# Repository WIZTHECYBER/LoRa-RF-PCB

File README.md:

# LoRa-RF-PCB

A custom PCB for long range radio frequency (LoRa) communication, built around an RP2040 and a Semtech SX1262 radio.

## Overview

I saw a guideline for a LoRa RF devboard in Forge Blueprint and decided to make my own. I did made schematics with help of AI and then designed and routed the PCB myself!!

###This PCB contains following components###
|MCU, radio, and flash all on one PCB, powered and programmed over USB-C.|

## Schematics Components 

| Part | Role |
|---|---|
| RP2040 | Microcontroller — runs everything |
| SX1262 | LoRa radio chip — handles the actual RF signal |
| 16MB flash | Stores the firmware |
| USB-C | Power and programming |
| RF switch + filter + antenna | Gets the signal in and out cleanly |
| Crystal oscillators | Reference clocks for the MCU and radio |
| LDO regulator | Power supply |
| Boot / Reset buttons | Standard flashing controls |

## Build Journey

This was my first time working with a 4-layer PCB, and it showed me why layer count matters — figuring it out took a while, but I learned a lot along the way. I used **Gemini** for help with the schematics.

From there, I moved on to placing components and routing the PCB myself. 

RF signal paths need to be straight and length-matched, which made that part of the routing genuinely tricky — it took about 2 days to fully route the board. Once the hardware was done, I wrote the firmware to bring it to life.

## Bill of Materials (BOM)

| Designator(s) | Part | Value / Footprint | Qty |
|---|---|---|---|
| U1 | RP2040 | Microcontroller, QFN-56 | 1 |
| U2 | SX1262IMLTRT | LoRa/FSK Transceiver, QFN-24 | 1 |
| U3 | W25Q128JVS | 16MB SPI Flash, SOIC-8 | 1 |
| U4 | PE4259 | RF Switch, SOT-363 | 1 |
| U5 | AP2112K-3.3 | 3.3V LDO Regulator, SOT-23-5 | 1 |
| USB_C | USB-C Receptacle | USB 2.0, 16-pin | 1 |
| J3 | Pin Socket, 1x04 | For a 0.96" OLED display | 1 |
| AE111 | U.FL Connector | For an external antenna | 1 |
| FL1 | Balun/Filter | Johanson 0900FM15K0039 | 1 |
| Y1 | Crystal | 32MHz (radio ref clock) | 1 |
| Y2 | Crystal | 12MHz (MCU ref clock) | 1 |
| BOOT | Tactile Switch | B3U-1000P | 1 |
| RESET | Tactile Switch | B3U-1000P | 1 |
| LED1 | LED | Blue | 1 |
| L1 | Inductor | 47nH | 1 |
| L2 | Inductor | 9.1nH | 1 |
| L3 | Inductor | 15µH (PA regulator) | 1 |
| R1 | Resistor | 100Ω | 1 |
| R2, R3, R7* | Resistor | 1kΩ | 3 |
| R4, R10 | Resistor | 10kΩ | 2 |
| R5, R6 | Resistor | 5.1kΩ (USB CC) | 2 |
| R8, R9 | Resistor | 27Ω (USB D+/D−) | 2 |
| R11, R12 | Resistor | 4.7kΩ | 2 |
| C1, C8, C9, C13, C14, C17–C23 | Capacitor | 100nF | 12 |
| C11, C12 | Capacitor | 27pF (crystal load) | 2 |
| C15, C16 | Capacitor | 1µF | 2 |
| C24, C25 | Capacitor | 10µF | 2 |
| C2 | Capacitor | 1nF | 1 |
| C3 | Capacitor | 39pF | 1 |
| C4, C5 | Capacitor | 3.3pF (RF matching) | 2 |
| C6 | Capacitor | 47pF | 1 |
| C7 | Capacitor | 47nF | 1 |
| C10 | Capacitor | 470nF (PA regulator) | 1 |

## Getting It Built

The RP2040, SX1262, and flash chip are all fine-pitch QFN parts, so this isn't a hand-soldering job — it needs PCBA (assembled by the fab) rather than a bare PCB.

## AI Use

Being upfront about it: I used Gemini for help with component selection and schematic routing, did the PCB design and routing myself!!.

## License

Released under [CERN-OHL-S](https://ohwr.org/cern_ohl_s_v2.txt) — feel free to fork it, fab it, and build on it.

Thanks for taking the time to look through this one — it was one of the more challenging boards I've built so far, and I learned a ton doing it. If you spot something worth improving, or you end up building one yourself, I'd genuinely love to hear about it. Feel free to open an issue or reach out.📡

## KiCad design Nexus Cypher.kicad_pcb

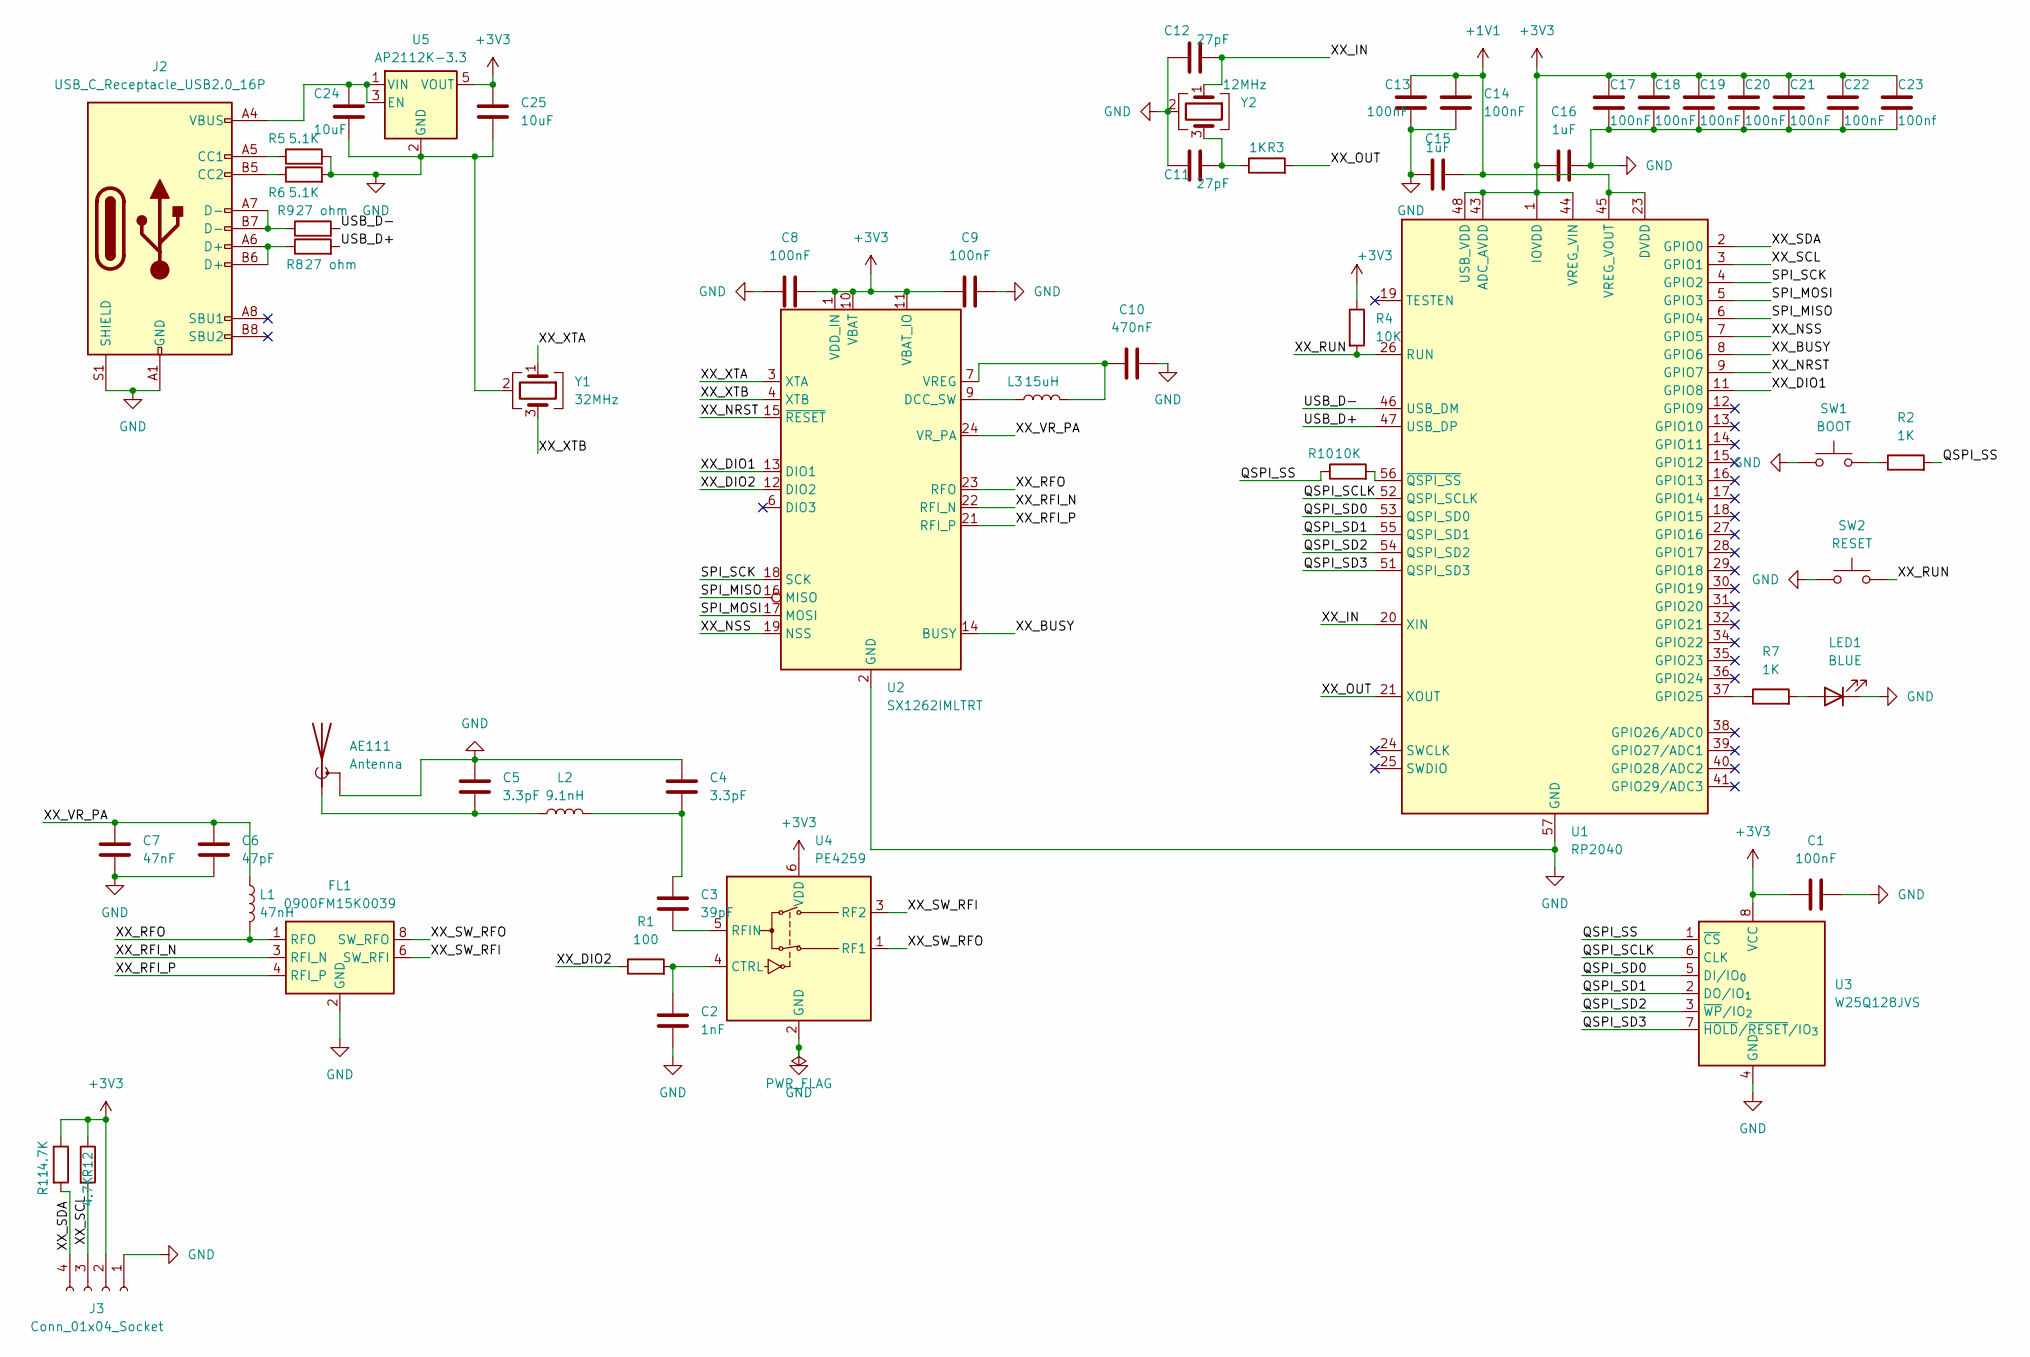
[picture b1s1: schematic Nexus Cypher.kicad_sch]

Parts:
AE111: Antenna; U.FL_Hirose_U.FL-R-SMT-1_Vertical
C1, C8, C9, C13, C14, C17, C18, C19, C20, C21, C22: 100nF; C_0603_1608Metric
C2: 1nF; C_0603_1608Metric
C3: 39pF; C_0603_1608Metric
C4, C5: 3.3pF; C_0603_1608Metric
C6: 47pF; C_0603_1608Metric
C7: 47nF; C_0603_1608Metric
C10: 470nF; C_0603_1608Metric
C11, C12: 27pF; C_0603_1608Metric
C15, C16: 1uF; C_0603_1608Metric
C23: 100nf; C_0603_1608Metric
C24, C25: 10uF; C_0805_2012Metric
FL1: 0900FM15K0039; Balun_Johanson_0900FM15K0039
J2: USB_C_Receptacle_USB2.0_16P; USB_C_Receptacle_HRO_TYPE-C-31-M-12
J3: Conn_01x04_Socket; PinSocket_1x04_P2.54mm_Vertical
L1: 47nH; L_0603_1608Metric
L2: 9.1nH; L_0603_1608Metric
L3: 15uH; L_0805_2012Metric
LED1: BLUE; LED_0603_1608Metric
R1: 100; R_0603_1608Metric
R2, R3, R7: 1K; R_0603_1608Metric
R4, R10: 10K; R_0603_1608Metric
R5, R6: 5.1K; R_0603_1608Metric
R8, R9: 27 ohm; R_0603_1608Metric
R11, R12: 4.7K; R_0603_1608Metric
SW1: BOOT; SW_SPST_B3U-1000P
SW2: RESET; SW_SPST_B3U-1000P
U1: RP2040; QFN-56-1EP_7x7mm_P0.4mm_EP3.2x3.2mm
U2: SX1262IMLTRT; QFN-24-1EP_4x4mm_P0.5mm_EP2.6x2.6mm
U3: W25Q128JVS; SOIC-8_5.3x5.3mm_P1.27mm
U4: PE4259; SOT-363_SC-70-6
U5: AP2112K-3.3; SOT-23-5
Y1: 32MHz; Crystal_SMD_3225-4Pin_3.2x2.5mm
Y2: 12MHz; Crystal_SMD_Abracon_ABM8G-4Pin_3.2x2.5mm

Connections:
+1V1: C13.1, C14.1, C15.2, U1.23 (DVDD), U1.45 (VREG_VOUT), U1.50 (DVDD)
+3V3: C1.1, C8.2, C9.1, C16.1, C17.1, C18.1, C19.1, C20.1, C21.1, C22.1, C23.1, C25.1, J3.2, R4.1, R11.1, R12.1, U1.1 (IOVDD), U1.10 (IOVDD), U1.22 (IOVDD), U1.33 (IOVDD), U1.42 (IOVDD), U1.43 (ADC_AVDD), U1.44 (VREG_VIN), U1.48 (USB_VDD), U1.49 (IOVDD), U2.1 (VDD_IN), U2.10 (VBAT), U2.11 (VBAT_IO), U3.8 (VCC), U4.6 (VDD), U5.5 (VOUT)
/QSPI_SCLK: U1.52 (QSPI_SCLK), U3.6 (CLK)
/QSPI_SD0: U1.53 (QSPI_SD0), U3.5 (DI/IO_{0})
/QSPI_SD1: U1.55 (QSPI_SD1), U3.2 (DO/IO_{1})
/QSPI_SD2: U1.54 (QSPI_SD2), U3.3 (~WP/IO_{2})
/QSPI_SD3: U1.51 (QSPI_SD3), U3.7 (~HOLD/~RESET/IO_{3})
/QSPI_SS: R2.2, R10.1, U3.1 (~CS)
/SPI_MISO: U1.6 (GPIO4), U2.16 (MISO)
/SPI_MOSI: U1.5 (GPIO3), U2.17 (MOSI)
/SPI_SCK: U1.4 (GPIO2), U2.18 (SCK)
/USB_D+: R8.2, U1.47 (USB_DP)
/USB_D-: R9.2, U1.46 (USB_DM)
/XX_BUSY: U1.8 (GPIO6), U2.14 (BUSY)
/XX_DIO1: U1.11 (GPIO8), U2.13 (DIO1)
/XX_DIO2: R1.1, U2.12 (DIO2)
/XX_IN: C12.2, U1.20 (XIN), Y2.1
/XX_NRST: U1.9 (GPIO7), U2.15 (~RESET)
/XX_NSS: U1.7 (GPIO5), U2.19 (NSS)
/XX_OUT: R3.2, U1.21 (XOUT)
/XX_RFI_N: FL1.3 (RFI_N), U2.22 (RFI_N)
/XX_RFI_P: FL1.4 (RFI_P), U2.21 (RFI_P)
/XX_RFO: FL1.1 (RFO), L1.2, U2.23 (RFO)
/XX_RUN: R4.2, SW2.2, U1.26 (RUN)
/XX_SCL: J3.3, R12.2, U1.3 (GPIO1)
/XX_SDA: J3.4, R11.2, U1.2 (GPIO0)
/XX_SW_RFI: FL1.6 (SW_RFI), U4.3 (RF2)
/XX_SW_RFO: FL1.8 (SW_RFO), U4.1 (RF1)
/XX_VR_PA: C6.1, C7.1, L1.1, U2.24 (VR_PA)
/XX_XTA: U2.3 (XTA), Y1.1
/XX_XTB: U2.4 (XTB), Y1.3
GND: AE111.2 (Shield), C1.2, C2.2, C4.2, C5.2, C6.2, C7.2, C8.1, C9.2, C10.2, C11.2, C12.1, C13.2, C14.2, C15.1, C16.2, C17.2, C18.2, C19.2, C20.2, C21.2, C22.2, C23.2, C24.2, C25.2, FL1.2 (GND), FL1.5 (GND), FL1.7 (GND), FL1.9 (GND), FL1.10 (GND), J2.A1 (GND), J2.A12 (GND), J2.B1 (GND), J2.B12 (GND), J2.S1 (SHIELD), J3.1, LED1.1 (K), R5.2, R6.2, SW1.1, SW2.1, U1.57 (GND), U2.2 (GND), U2.5 (GND), U2.8 (GND), U2.20 (GND), U2.25 (GND), U3.4 (GND), U4.2 (GND), U5.2 (GND), Y1.2 (G), Y1.4 (G), Y2.2 (G), Y2.4 (G)
unnamed: AE111.1 (A), C5.1, L2.1
unnamed: C3.1, C4.1, L2.2
unnamed: C11.1, R3.1, Y2.3
unnamed: J2.A5 (CC1), R5.1
unnamed: J2.B5 (CC2), R6.1
unnamed: J2.A6 (D+), J2.B6 (D+), R8.1
unnamed: J2.A7 (D-), J2.B7 (D-), R9.1
unnamed: LED1.2 (A), R7.2
unnamed: R2.1, SW1.2
unnamed: R7.1, U1.37 (GPIO25)
unnamed: R10.2, U1.56 (~QSPI_SS)
unnamed: L3.1, U2.9 (DCC_SW)
unnamed: C10.1, L3.2, U2.7 (VREG)
unnamed: C2.1, R1.2, U4.4 (CTRL)
unnamed: C3.2, U4.5 (RFIN)
unnamed: C24.1, J2.A4 (VBUS), J2.A9 (VBUS), J2.B4 (VBUS), J2.B9 (VBUS), U5.1 (VIN), U5.3 (EN)

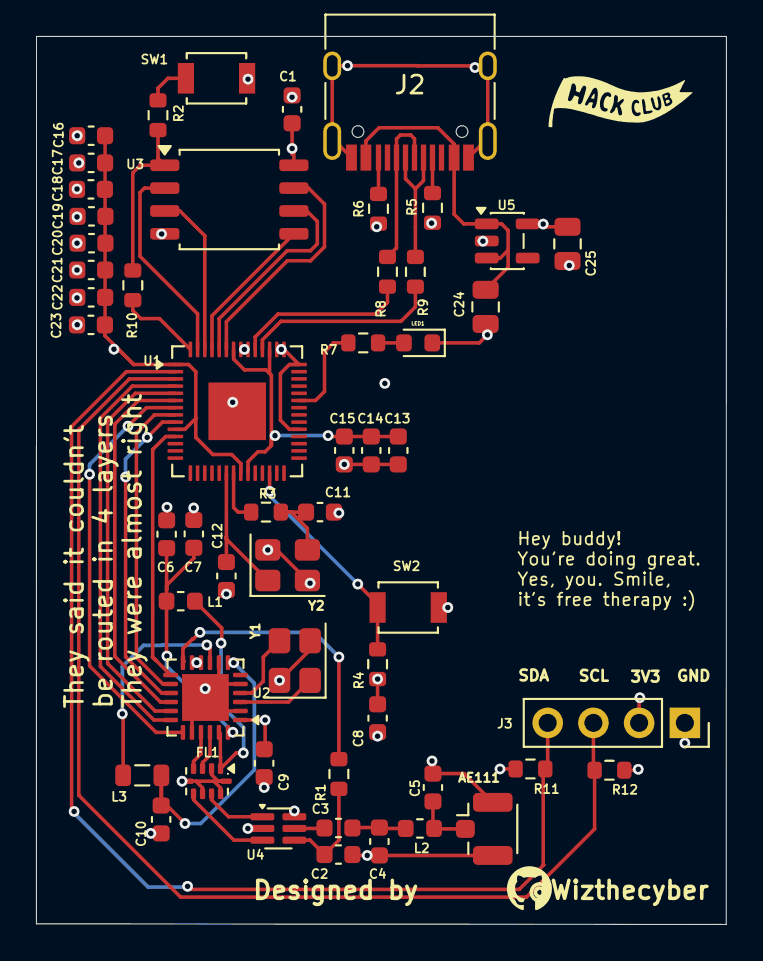
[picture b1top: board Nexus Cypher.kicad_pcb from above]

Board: 4 copper layers, 38.3 x 49.3 mm, 54 parts (0 on the bottom side), 48 nets.

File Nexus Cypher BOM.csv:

"Id";"Designator";"Footprint";"Quantity";"Designation";"Supplier and ref";
1;"AE111";"U.FL_Hirose_U.FL-R-SMT-1_Vertical";1;"Antenna";;;
2;"boot";"SW_SPST_B3U-1000P";1;"BOOT";;;
3;"C1, C8, C9, C13, C14, C17, C18, C19, C20, C21, C22";"C_0603_1608Metric";11;"100nF";;;
4;"C2";"C_0603_1608Metric";1;"1nF";;;
5;"C3";"C_0603_1608Metric";1;"39pF";;;
6;"C4, C5";"C_0603_1608Metric";2;"3.3pF";;;
7;"C6";"C_0603_1608Metric";1;"47pF";;;
8;"C7";"C_0603_1608Metric";1;"47nF";;;
9;"C10";"C_0603_1608Metric";1;"470nF";;;
10;"C11, C12";"C_0603_1608Metric";2;"27pF";;;
11;"C15, C16";"C_0603_1608Metric";2;"1uF";;;
12;"C23";"C_0603_1608Metric";1;"100nf";;;
13;"C24, C25";"C_0805_2012Metric";2;"10uF";;;
14;"FL1";"Balun_Johanson_0900FM15K0039";1;"0900FM15K0039";;;
15;"J3";"PinSocket_1x04_P2.54mm_Vertical";1;"Conn_01x04_Socket";;;
16;"L1";"L_0603_1608Metric";1;"47nH";;;
17;"L2";"L_0603_1608Metric";1;"9.1nH";;;
18;"L3";"L_0805_2012Metric";1;"15uH";;;
19;"LED1";"LED_0603_1608Metric";1;"BLUE";;;
20;"R1";"R_0603_1608Metric";1;"100";;;
21;"R1K, R3, R7";"R_0603_1608Metric";3;"1K";;;
22;"R4, R10";"R_0603_1608Metric";2;"10K";;;
23;"R5, R6";"R_0603_1608Metric";2;"5.1K";;;
24;"R8, R9";"R_0603_1608Metric";2;"27 ohm";;;
25;"R11, R12";"R_0603_1608Metric";2;"4.7K";;;
26;"SW2";"SW_SPST_B3U-1000P";1;"RESET";;;
27;"U1";"QFN-56-1EP_7x7mm_P0.4mm_EP3.2x3.2mm";1;"RP2040";;;
28;"U2";"QFN-24-1EP_4x4mm_P0.5mm_EP2.6x2.6mm";1;"SX1262IMLTRT";;;
29;"U3";"SOIC-8_5.3x5.3mm_P1.27mm";1;"W25Q128JVS";;;
30;"U4";"SOT-363_SC-70-6";1;"PE4259";;;
31;"U5";"SOT-23-5";1;"AP2112K-3.3";;;
32;"USB-C_RECEPTACLE";"USB_C_Receptacle_HRO_TYPE-C-31-M-12";1;"USB_C_Receptacle_USB2.0_16P";;;
33;"Y1";"Crystal_SMD_3225-4Pin_3.2x2.5mm_HandSoldering";1;"32MHz";;;
34;"Y2";"Crystal_SMD_3225-4Pin_3.2x2.5mm_HandSoldering";1;"12MHz";;;

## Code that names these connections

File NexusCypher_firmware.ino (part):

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 * ATTACH THE ANTENNA (U.FL) BEFORE POWERING ON.
 *
 * PIN MAP (from the board schematic)
 *   SX1262 SPI0: SCK=GPIO2  MOSI=GPIO3  MISO=GPIO4  NSS=GPIO5
 *   SX1262 BUSY=GPIO6  RESET=GPIO7  DIO1=GPIO8
 *   DIO2 drives the PE4259 RF switch directly (handled by the radio)
 *   Status LED = GPIO25    OLED header J3 (I2C0): SDA=GPIO0  SCL=GPIO1
 *   BOOT / RESET buttons are hardware-only (bootsel / RUN), not readable.
 */

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

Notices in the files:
README.md:
License: CERN-OHL-S
